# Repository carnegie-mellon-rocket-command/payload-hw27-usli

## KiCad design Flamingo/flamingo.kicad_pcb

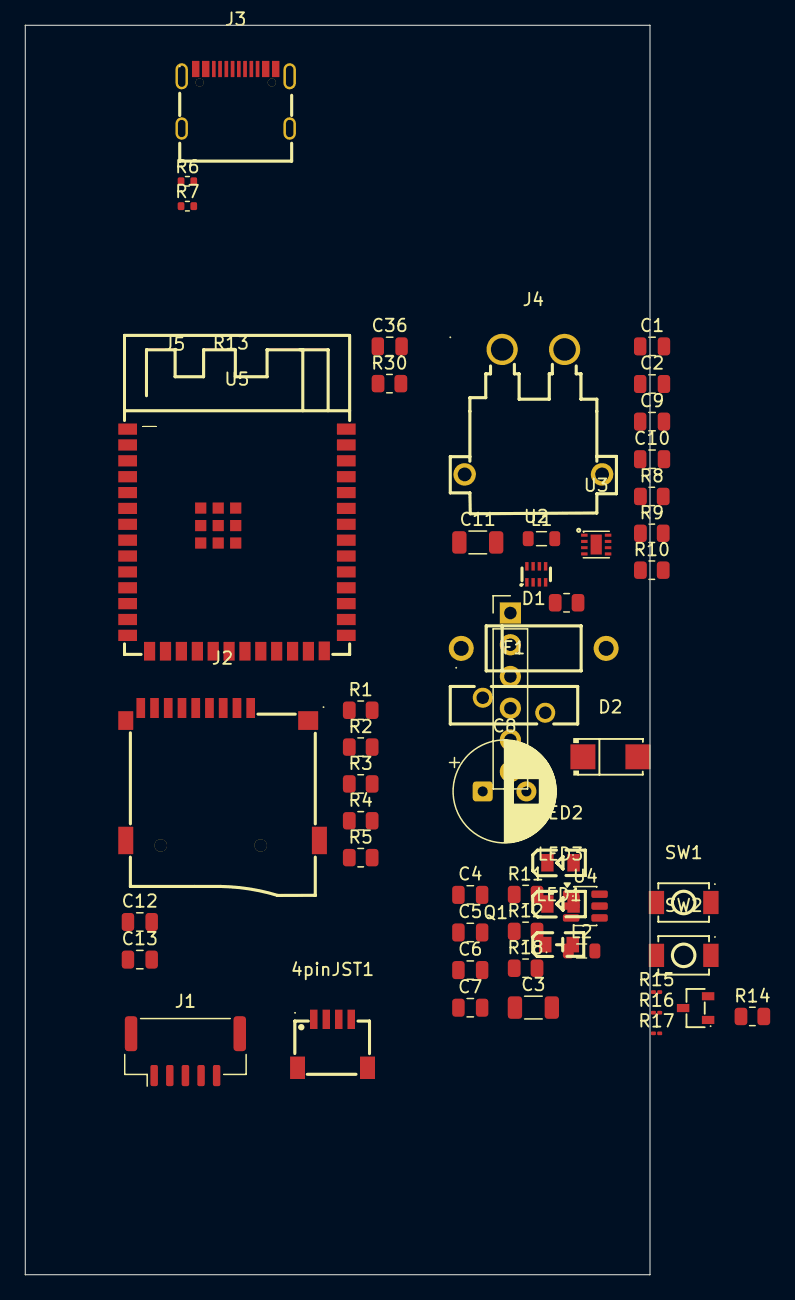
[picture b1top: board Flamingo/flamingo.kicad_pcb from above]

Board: 2 copper layers, 50.0 x 100.0 mm, 54 parts (0 on the bottom side), 43 nets, no tracks yet.

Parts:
4pinJST1: SM04B-SRSS-TB; CONN-SMD_4P-P1.00_SM04B-SRSS-TB-LF-SN
C1, C13: 10uF; C_0805_2012Metric
C2, C4, C5: 22uF; C_0805_2012Metric
C3: 10uF; C_1206_3216Metric
C6, C7, C12: 0.1uF; C_0805_2012Metric
C8: 47uF; CP_Radial_D8.0mm_P3.50mm
C9, C10: 4.7uF; C_0805_2012Metric
C11: 100uF; C_1206_3216Metric
C36: 1uF; C_0805_2012Metric
D1: P6KE20A; DO-15_BD3.1-L6.7-P10.70-D0.9-RD
D2: SS34; SMA_L4.3-W2.6-LS5.2-RD
F1: MF-R160; FUSE-TH_L10.2-W3.0-P5.10-D0.8-S1.20
J1: STA-M020X; JST_GH_BM05B-GHS-TBT_1x05-1MP_P1.25mm_Vertical
J2: TF-115-BCP9; TF-SMD_TF-115-BCP9
J3: USB-TYPE-C-017; USB-TYPE-C-SMD_C9900008089
J4: XT30PW-M30.G.Y; CONN-TH_XT30PW-M
J5: ARDUCAM_MEGA_SPI; PinHeader_1x06_P2.54mm_Vertical
L1: 2.2uH; L_0805_2012Metric
L2: 10uH; L_0805_2012Metric
LED1: XL-2012SURC; LED0805-RD
LED2, LED3: 0805G; LED0805-R-RD
Q1: AO3400A; SOT-23-3_L2.9-W1.3-P1.90-LS2.4-BR
R1, R2, R3, R4, R5, R8, R11, R13, R30: 10k; R_0805_2012Metric
R6, R7: 5.1k; R_0402_1005Metric
R9: 33k; R_0805_2012Metric
R10, R14, R18: 100k; R_0805_2012Metric
R12: 3.3k; R_0805_2012Metric
R15: 470; R_01005_0402Metric
R16, R17: 1k; R_01005_0402Metric
SW1, SW2: TS-1088-AR02016; SW-SMD_L3.9-W3.0-P4.45
U2: TPS2116DRLR; SOT-583-8_L2.1-W1.6-P0.50-LS1.6-BL
U3: TPS62162DSGR; WSON-8_L2.0-W2.0-P0.50-TL-EP
U4: TPS54302DDCR; SOT-23-6
U5: ESP32-S3-WROOM-1; WIRELM-SMD_ESP32-S3-WROOM-1

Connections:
3V3: J5.1, R13.2, R17.2
+3V3: C2.1, C12.1, C13.1, J2.4 (VDD), L1.2, R1.1, R2.1, R3.1, R4.1, R5.1, R10.2, R30.1, U3.6 (VOS), U5.2 (3V3)
/Arducam Mega SPI camera/CAM_CS: J5.6, R13.1, U5.7 (IO7)
/Arducam Mega SPI camera/CAM_MISO: J5.4, U5.17 (IO9)
/Arducam Mega SPI camera/CAM_MOSI: J5.5, U5.18 (IO10)
/Arducam Mega SPI camera/CAM_SCK: J5.3, U5.12 (IO8)
/Debug/DIAG_FAULT: R15.2, U5.11 (IO18)
/Debug/DIAG_HEARTBEAT: R16.2, U5.23 (IO21)
/Debug/DIAG_LED_EN: Q1.1 (G), R14.1, U5.10 (IO17)
/Debug/ESP_BOOT: SW2.1, U5.27 (IO0)
/Debug/LED_RETURN: LED1.1 (-), LED2.2 (K), Q1.3 (D)
/ESP32-S3 core/FC_UART_RX: 4pinJST1.3, U5.38 (IO2)
/ESP32-S3 core/FC_UART_TX: 4pinJST1.4, U5.39 (IO1)
/ESP32-S3 core/LASER_RX: J1.4, U5.32 (IO39)
/ESP32-S3 core/LASER_TX: J1.3, U5.31 (IO38)
/ESP32-S3 core/SD_CLK: J2.5 (CLK), U5.33 (IO40)
/ESP32-S3 core/USB_D_N: J3.A7 (DN1), J3.B7 (DN2), U5.13 (IO19)
/ESP32-S3 core/USB_D_P: J3.A6 (DP1), J3.B6 (DP2), U5.14 (IO20)
/Power/4S to 5 V buck/VBAT_PROT: C3.1, C6.1, C8.1, D1.1 (C), D2.1 (K), U4.3 (VIN)
/Power/BUCK_5V: C4.1, C5.1, C9.2, L2.2, R18.1, U2.6 (VIN2)
/Power/Input Protection/VBAT_4S: F1.1, J4.2 (+)
/Power/PR1: R8.2, R9.1, U2.4 (PR1)
/Power/USB_5V: C10.2, J3.A4B9 (VBUS), J3.B4A9 (VBUS), R9.2, U2.3 (VIN1), U2.5 (MODE)
/microSD/SD_CS: J2.2 (CD/DATA3), R2.2, U5.24 (IO47)
/microSD/SD_DAT1: J2.8 (DAT1), R5.2
/microSD/SD_DAT2: J2.1 (DATA2), R1.2
/microSD/SD_MISO: J2.7 (DAT0), R4.2, U5.35 (IO42)
/microSD/SD_MOSI: J2.3 (CMD), R3.2, U5.34 (IO41)
ESP_EN: C36.1, R30.2, SW1.1, U5.3 (EN)
GND: 4pinJST1.1, 4pinJST1.5, 4pinJST1.6, C1.2, C2.2, C3.2, C4.2, C5.2, C6.2, C8.2, C9.1, C10.1, C11.1, C12.2, C13.2, C36.2, D1.2 (A), J1.1, J2.6 (VSS), J2.10 (GND), J2.11 (GND), J2.12 (GND), J2.13 (GND), J3.1, J3.2, J3.3, J3.4, J3.A1B12 (GND), J3.B1A12 (GND), J4.1 (-), J4.3, J4.4, J5.2, LED3.2 (K), Q1.2 (S), R6.2, R7.2, R8.1, R12.1, R14.2, SW1.2, SW2.2, U2.1 (GND), U3.1 (PGND), U3.4 (AGND), U3.5 (FB), U3.9 (EP), U4.1 (GND), U5.1 (GND), U5.40 (GND), U5.41 (GND)
unnamed: D2.2 (A), F1.2
unnamed: J3.A5 (CC1), R7.1
unnamed: J3.B5 (CC2), R6.1
unnamed: LED1.2 (+), R15.1
unnamed: LED2.1 (A), R16.1
unnamed: LED3.1 (A), R17.1
unnamed: R11.1, R12.2
unnamed: R10.1, U3.8 (PG)
unnamed: L1.1, U3.7 (SW)
unnamed: C7.1, U4.6 (BOOT)
unnamed: R11.2, R18.2, U4.4 (FB)
unnamed: C7.2, L2.1, U4.2 (SW)
SYS_5V: C1.1, C11.2, J1.2, U2.2 (VOUT), U2.7 (VOUT), U3.2 (VIN), U3.3 (EN)

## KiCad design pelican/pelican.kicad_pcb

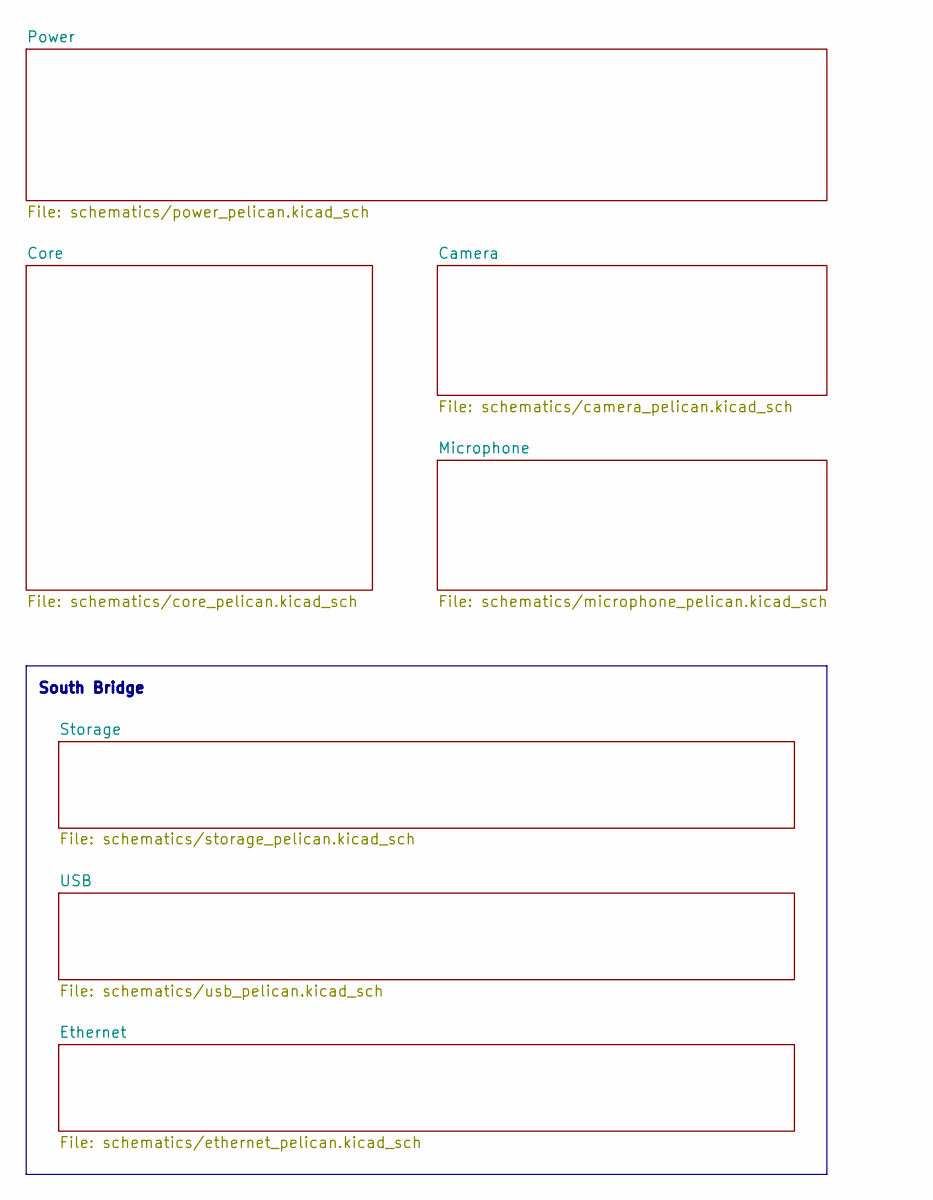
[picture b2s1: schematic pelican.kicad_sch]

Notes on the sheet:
South Bridge

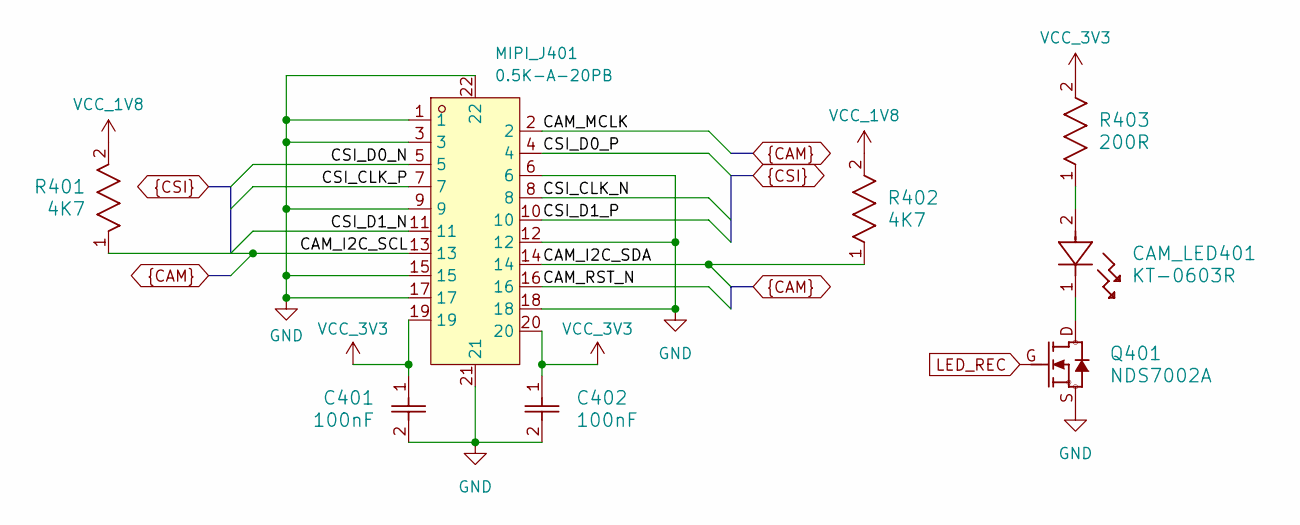
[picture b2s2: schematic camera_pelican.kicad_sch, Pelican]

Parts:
C401, C402: 100nF; C_GRM155R71C104KA88D; LCSC Part # C1525
CAM_LED401: KT-0603R; LED_LTST-C193KRKT-5A; LCSC Part # C2286
MIPI_J401: 0.5K-A-20PB; J_0.5K-A-20PB; MPN 0.5K-A-20PB; LCSC Part C2914144
Q401: NDS7002A; Q_NDS7002A; LCSC Part # C74715
R401, R402: 4K7; R_RC0402FR; LCSC Part # C25900
R403: 200R; R_RC0402FR; LCSC Part # C25087

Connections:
CAM_I2C_SCL: MIPI_J401.13, R401.1; also elsewhere on the board
CAM_I2C_SDA: MIPI_J401.14, R402.1; also elsewhere on the board
CAM_MCLK: MIPI_J401.2; also elsewhere on the board
CAM_RST_N: MIPI_J401.16; also elsewhere on the board
CSI_CLK_N: MIPI_J401.8; also elsewhere on the board
CSI_CLK_P: MIPI_J401.7; also elsewhere on the board
CSI_D0_N: MIPI_J401.5; also elsewhere on the board
CSI_D0_P: MIPI_J401.4; also elsewhere on the board
CSI_D1_N: MIPI_J401.11; also elsewhere on the board
CSI_D1_P: MIPI_J401.10; also elsewhere on the board
GND: C401.2, C402.2, MIPI_J401.1, MIPI_J401.3, MIPI_J401.6, MIPI_J401.9, MIPI_J401.12, MIPI_J401.15, MIPI_J401.17, MIPI_J401.18, MIPI_J401.21, MIPI_J401.22, Q401.S; also elsewhere on the board
LED_REC: Q401.G; also elsewhere on the board
unnamed: CAM_LED401.1, Q401.D
unnamed: CAM_LED401.2, R403.1
VCC_1V8: R401.2, R402.2; also elsewhere on the board
VCC_3V3: C401.1, C402.1, MIPI_J401.19, MIPI_J401.20, R403.2; also elsewhere on the board

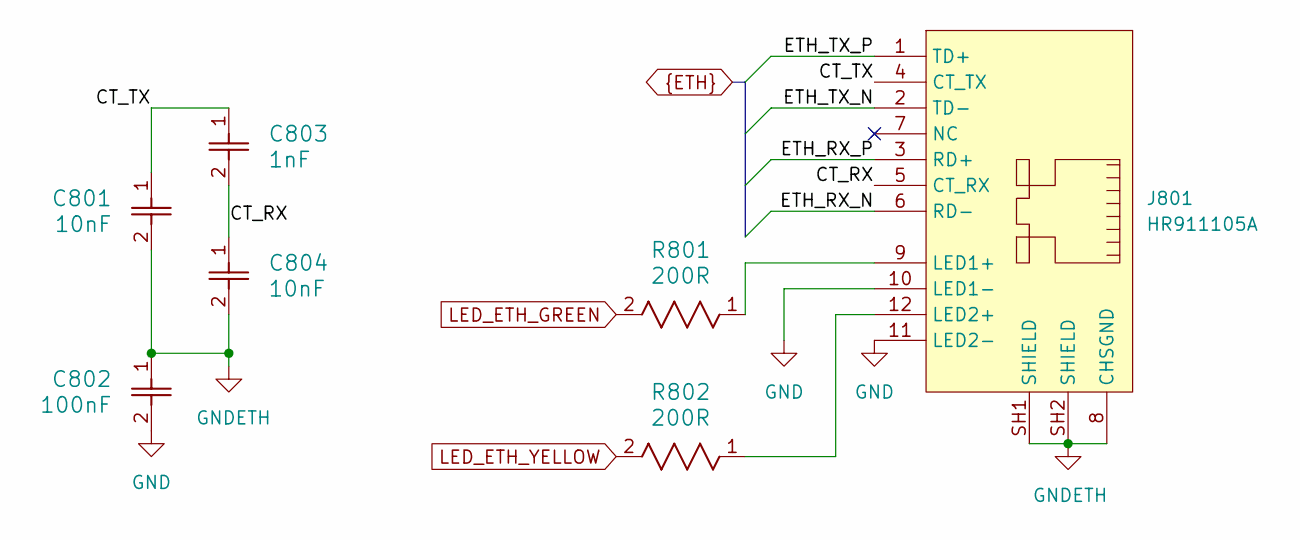
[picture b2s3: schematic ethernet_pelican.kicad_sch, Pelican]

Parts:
C801, C804: 10nF; C_CL05B103KO5NNNC; MPN CL05B103KO5NNNC; LCSC Part # C15195
C802: 100nF; C_GRM155R71C104KA88D; LCSC Part # C1525
C803: 1nF; C_CC0603CG100V102JN; MPN CC0603CG100V102JN; LCSC Part # C53084479
J801: HR911105A; J_HR911105A_TH; MPN HR911105A; LCSC Part C12074
R801, R802: 200R; R_RC0402FR; LCSC Part # C25087

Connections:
/Ethernet/CT_RX: C803.2, C804.1, J801.5 (CT_RX)
/Ethernet/CT_TX: C801.1, C803.1, J801.4 (CT_TX)
ETH_RX_N: J801.6 (RD-); also elsewhere on the board
ETH_RX_P: J801.3 (RD+); also elsewhere on the board
ETH_TX_N: J801.2 (TD-); also elsewhere on the board
ETH_TX_P: J801.1 (TD+); also elsewhere on the board
GND: C802.2, J801.10 (LED1-), J801.11 (LED2-); also elsewhere on the board
GNDETH: C801.2, C802.1, C804.2, J801.8 (CHSGND), J801.SH1 (SHIELD), J801.SH2 (SHIELD)
LED_ETH_GREEN: R801.2; also elsewhere on the board
LED_ETH_YELLOW: R802.2; also elsewhere on the board
unnamed: J801.9 (LED1+), R801.1
unnamed: J801.12 (LED2+), R802.1

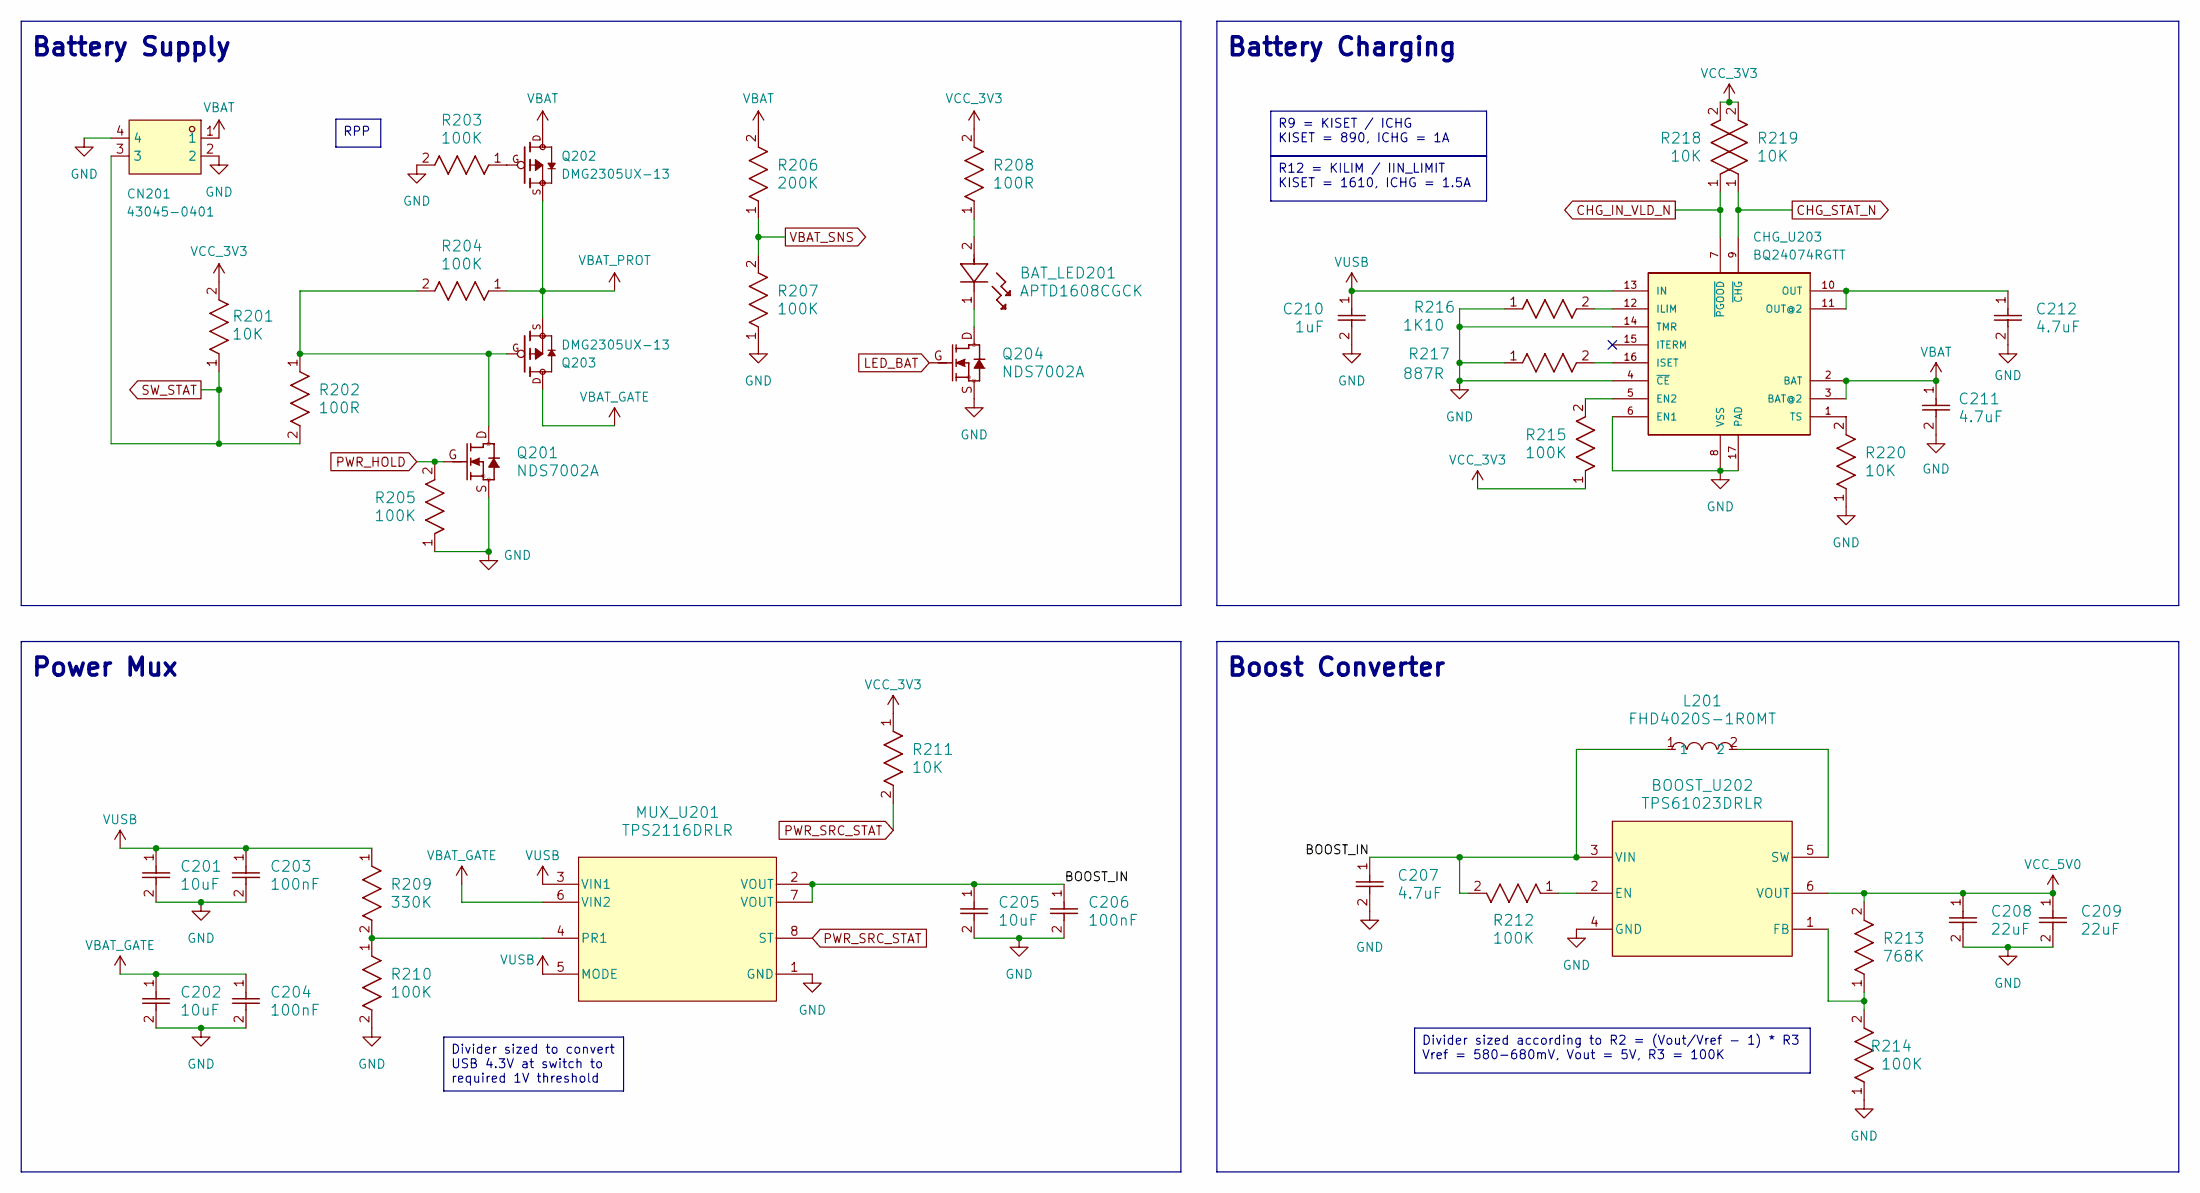
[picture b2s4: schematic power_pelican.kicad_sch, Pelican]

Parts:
BAT_LED201: APTD1608CGCK; LED_LTST-C193KGKT-5A; LCSC Part # C5121471
BOOST_U202: TPS61023DRLR; U_TPS61023DRLR; LCSC Part # C919459
C201, C202, C205: 10uF; C_GRM155R61A106ME11D; LCSC Part # C408132
C203, C204, C206: 100nF; C_GRM155R71C104KA88D; LCSC Part # C1525
C207, C211, C212: 4.7uF; C_GRM188R61A475KE15D; LCSC Part # C19666
C208, C209: 22uF; C_GRM188R61A226ME15D; LCSC Part # C84419
C210: 1uF; C_GRM155R61A105KE15D; LCSC Part # C52923
CHG_U203: BQ24074RGTT; U_BQ24074RGTT; LCSC Part # C2861252
CN201: 43045-0401; J_43045-0401_2x02_RA; MPN 430450401; LCSC Part C585880
L201: FHD4020S-1R0MT; L_FHD4020S-1R0MT; MPN FHD4020S-1R0MT; LCSC Part # C602028
MUX_U201: TPS2116DRLR; U_TPS2116DRLR; LCSC Part # C3235557
Q201, Q204: NDS7002A; Q_NDS7002A; LCSC Part # C74715
Q202, Q203: DMG2305UX-13; Q_DMG2305UX-13; PARTREV 09/2018; LCSC Part # C144153
R201, R211, R218, R219, R220: 10K; R_RC0402FR; LCSC Part # C25744
R202, R208: 100R; R_RC0402FR; LCSC Part # C25076
R203, R204, R205, R207, R210, R212, R214, R215: 100K; R_RC0402FR; LCSC Part # C25741
R206: 200K; R_RC0402FR; LCSC Part # C25764
R209: 330K; R_RC0402FR; LCSC Part # C25778
R213: 768K; R_RC0402FR; LCSC Part # C273722
R216: 1K10; R_RC0402FR; LCSC Part # C25860
R217: 887R; R_RC0402FR; LCSC Part # C477810

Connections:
/Power/BOOST_IN: BOOST_U202.3 (VIN), C205.1, C206.1, C207.1, L201.1, MUX_U201.2 (VOUT), MUX_U201.7 (VOUT), R212.2
CHG_IN_VLD_N: CHG_U203.7 (~PGOOD), R218.1; also elsewhere on the board
CHG_STAT_N: CHG_U203.9 (~CHG), R219.1; also elsewhere on the board
GND: BOOST_U202.4 (GND), C201.2, C202.2, C203.2, C204.2, C205.2, C206.2, C207.2, C208.2, C209.2, C210.2, C211.2, C212.2, CHG_U203.4 (~CE), CHG_U203.6 (EN1), CHG_U203.8 (VSS), CHG_U203.14 (TMR), CHG_U203.17 (PAD), CN201.2, CN201.4, MUX_U201.1 (GND), Q201.S, Q204.S, R203.2, R205.1, R207.1, R210.2, R214.1, R216.1, R217.1, R220.1; also elsewhere on the board
LED_BAT: Q204.G; also elsewhere on the board
unnamed: BAT_LED201.1, Q204.D
unnamed: BAT_LED201.2, R208.1
unnamed: BOOST_U202.2 (EN), R212.1
unnamed: BOOST_U202.1 (FB), R213.1, R214.2
unnamed: BOOST_U202.5 (SW), L201.2
unnamed: CHG_U203.5 (EN2), R215.2
unnamed: CHG_U203.12 (ILIM), R216.2
unnamed: CHG_U203.16 (ISET), R217.2
unnamed: C212.1, CHG_U203.10 (OUT), CHG_U203.11 (OUT@2)
unnamed: CHG_U203.1 (TS), R220.2
unnamed: MUX_U201.4 (PR1), R209.2, R210.1
unnamed: Q201.D, Q203.G, R202.1, R204.2
unnamed: Q202.G, R203.1
unnamed: Q202.S, Q203.S, R204.1
PWR_HOLD: Q201.G, R205.2; also elsewhere on the board
PWR_SRC_STAT: MUX_U201.8 (ST), R211.2; also elsewhere on the board
SW_STAT: CN201.3, R201.1, R202.2; also elsewhere on the board
VBAT: C211.1, CHG_U203.2 (BAT), CHG_U203.3 (BAT@2), CN201.1, Q202.D, R206.2
VBAT_SNS: R206.1, R207.2; also elsewhere on the board
VCC_3V3: R201.2, R208.2, R211.1, R215.1, R218.2, R219.2; also elsewhere on the board
VCC_5V0: BOOST_U202.6 (VOUT), C208.1, C209.1, R213.2; also elsewhere on the board
VUSB: C201.1, C203.1, C210.1, CHG_U203.13 (IN), MUX_U201.3 (VIN1), MUX_U201.5 (MODE), R209.1; also elsewhere on the board

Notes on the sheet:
Battery Charging
Power Mux
Battery Supply
Boost Converter
Divider sized according to R2 = (Vout/Vref - 1) * R3 Vref = 580-680mV, Vout = 5V, R3 = 100K
R12 = KILIM / IIN_LIMIT KISET = 1610, ICHG = 1.5A
R9 = KISET / ICHG KISET = 890, ICHG = 1A
Divider sized to convert USB 4.3V at switch to required 1V threshold
RPP

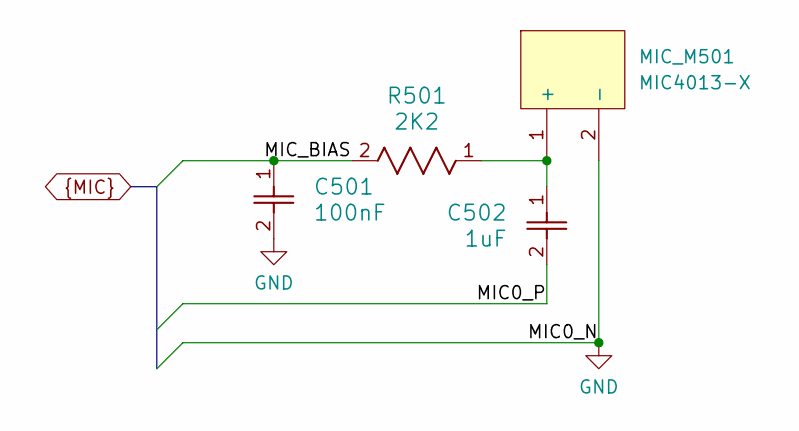
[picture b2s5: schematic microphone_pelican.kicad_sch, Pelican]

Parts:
C501: 100nF; C_GRM155R71C104KA88D; LCSC Part # C1525
C502: 1uF; C_GRM155R61A105KE15D; LCSC Part # C52923
MIC_M501: MIC4013-X; M_MIC4013-X; MPN MIC4013-X; LCSC Part # C49118137
R501: 2K2; R_RC0402FR; LCSC Part # C25879

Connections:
GND: C501.2, MIC_M501.2 (-); also elsewhere on the board
MIC0_P: C502.2; also elsewhere on the board
MIC_BIAS: C501.1, R501.2; also elsewhere on the board
unnamed: C502.1, MIC_M501.1 (+), R501.1

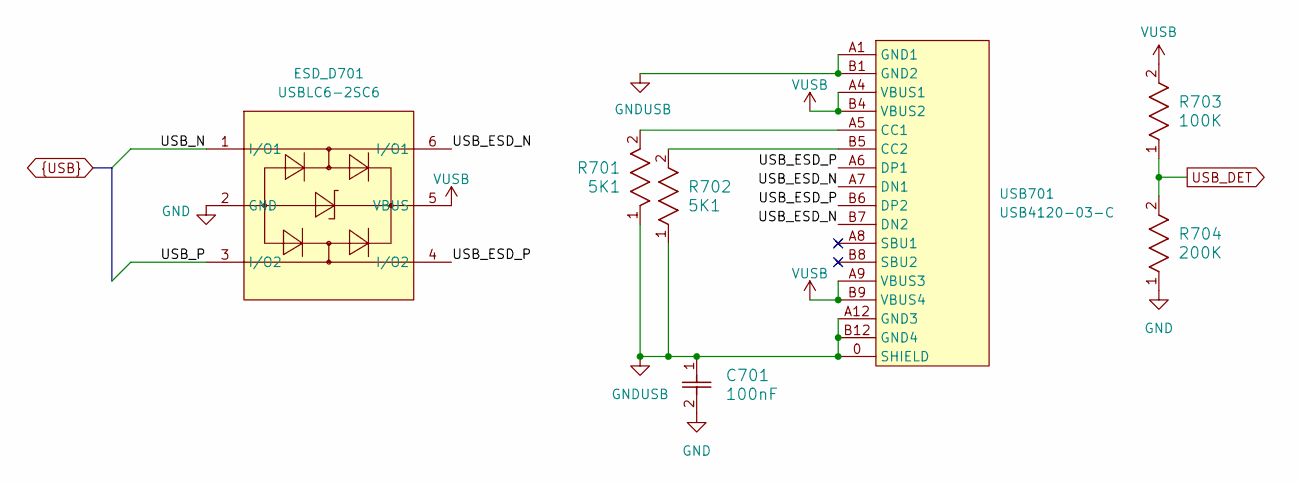
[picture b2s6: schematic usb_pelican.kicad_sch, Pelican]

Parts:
C701: 100nF; C_GRM155R71C104KA88D; LCSC Part # C1525
ESD_D701: USBLC6-2SC6; D_USBLC6-2SC6; MPN USBLC6-2SC6; LCSC Part # C7519
R701, R702: 5K1; R_RC0402FR; LCSC Part # C25905
R703: 100K; R_RC0402FR; LCSC Part # C25741
R704: 200K; R_RC0402FR; LCSC Part # C25764
USB701: USB4120-03-C; J_USB4120-03-C_SMD; MPN USB4120-03-C; LCSC Part C3445864

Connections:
/USB/USB_ESD_N: ESD_D701.6 (I/O1), USB701.A7 (DN1), USB701.B7 (DN2)
/USB/USB_ESD_P: ESD_D701.4 (I/O2), USB701.A6 (DP1), USB701.B6 (DP2)
GND: C701.2, ESD_D701.2 (GND), R704.1; also elsewhere on the board
GNDUSB: C701.1, R701.1, R702.1, USB701.0 (SHIELD), USB701.A1 (GND1), USB701.A12 (GND3), USB701.B1 (GND2), USB701.B12 (GND4)
unnamed: R701.2, USB701.A5 (CC1)
unnamed: R702.2, USB701.B5 (CC2)
USB_DET: R703.1, R704.2; also elsewhere on the board
USB_N: ESD_D701.1 (I/O1); also elsewhere on the board
USB_P: ESD_D701.3 (I/O2); also elsewhere on the board
VUSB: ESD_D701.5 (VBUS), R703.2, USB701.A4 (VBUS1), USB701.A9 (VBUS3), USB701.B4 (VBUS2), USB701.B9 (VBUS4); also elsewhere on the board

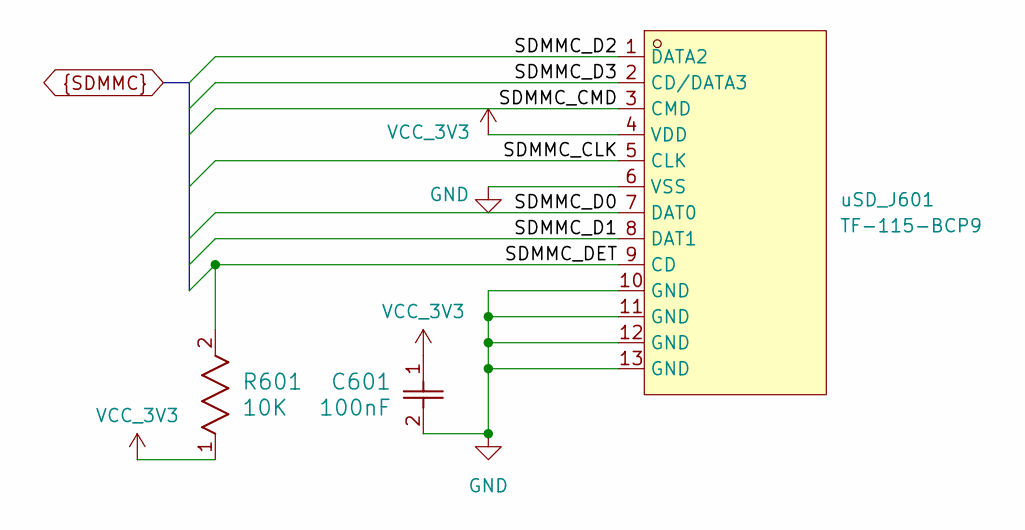
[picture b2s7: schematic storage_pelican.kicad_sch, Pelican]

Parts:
C601: 100nF; C_GRM155R71C104KA88D; LCSC Part # C1525
R601: 10K; R_RC0402FR; LCSC Part # C25744
uSD_J601: TF-115-BCP9; J_TF-115-BCP9; MPN TF-115-BCP9; LCSC Part # C720505

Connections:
GND: C601.2, uSD_J601.6 (VSS), uSD_J601.10 (GND), uSD_J601.11 (GND), uSD_J601.12 (GND), uSD_J601.13 (GND); also elsewhere on the board
SDMMC_CLK: uSD_J601.5 (CLK); also elsewhere on the board
SDMMC_CMD: uSD_J601.3 (CMD); also elsewhere on the board
SDMMC_D0: uSD_J601.7 (DAT0); also elsewhere on the board
SDMMC_D1: uSD_J601.8 (DAT1); also elsewhere on the board
SDMMC_D2: uSD_J601.1 (DATA2); also elsewhere on the board
SDMMC_D3: uSD_J601.2 (CD/DATA3); also elsewhere on the board
SDMMC_DET: R601.2, uSD_J601.9 (CD); also elsewhere on the board
VCC_3V3: C601.1, R601.1, uSD_J601.4 (VDD); also elsewhere on the board

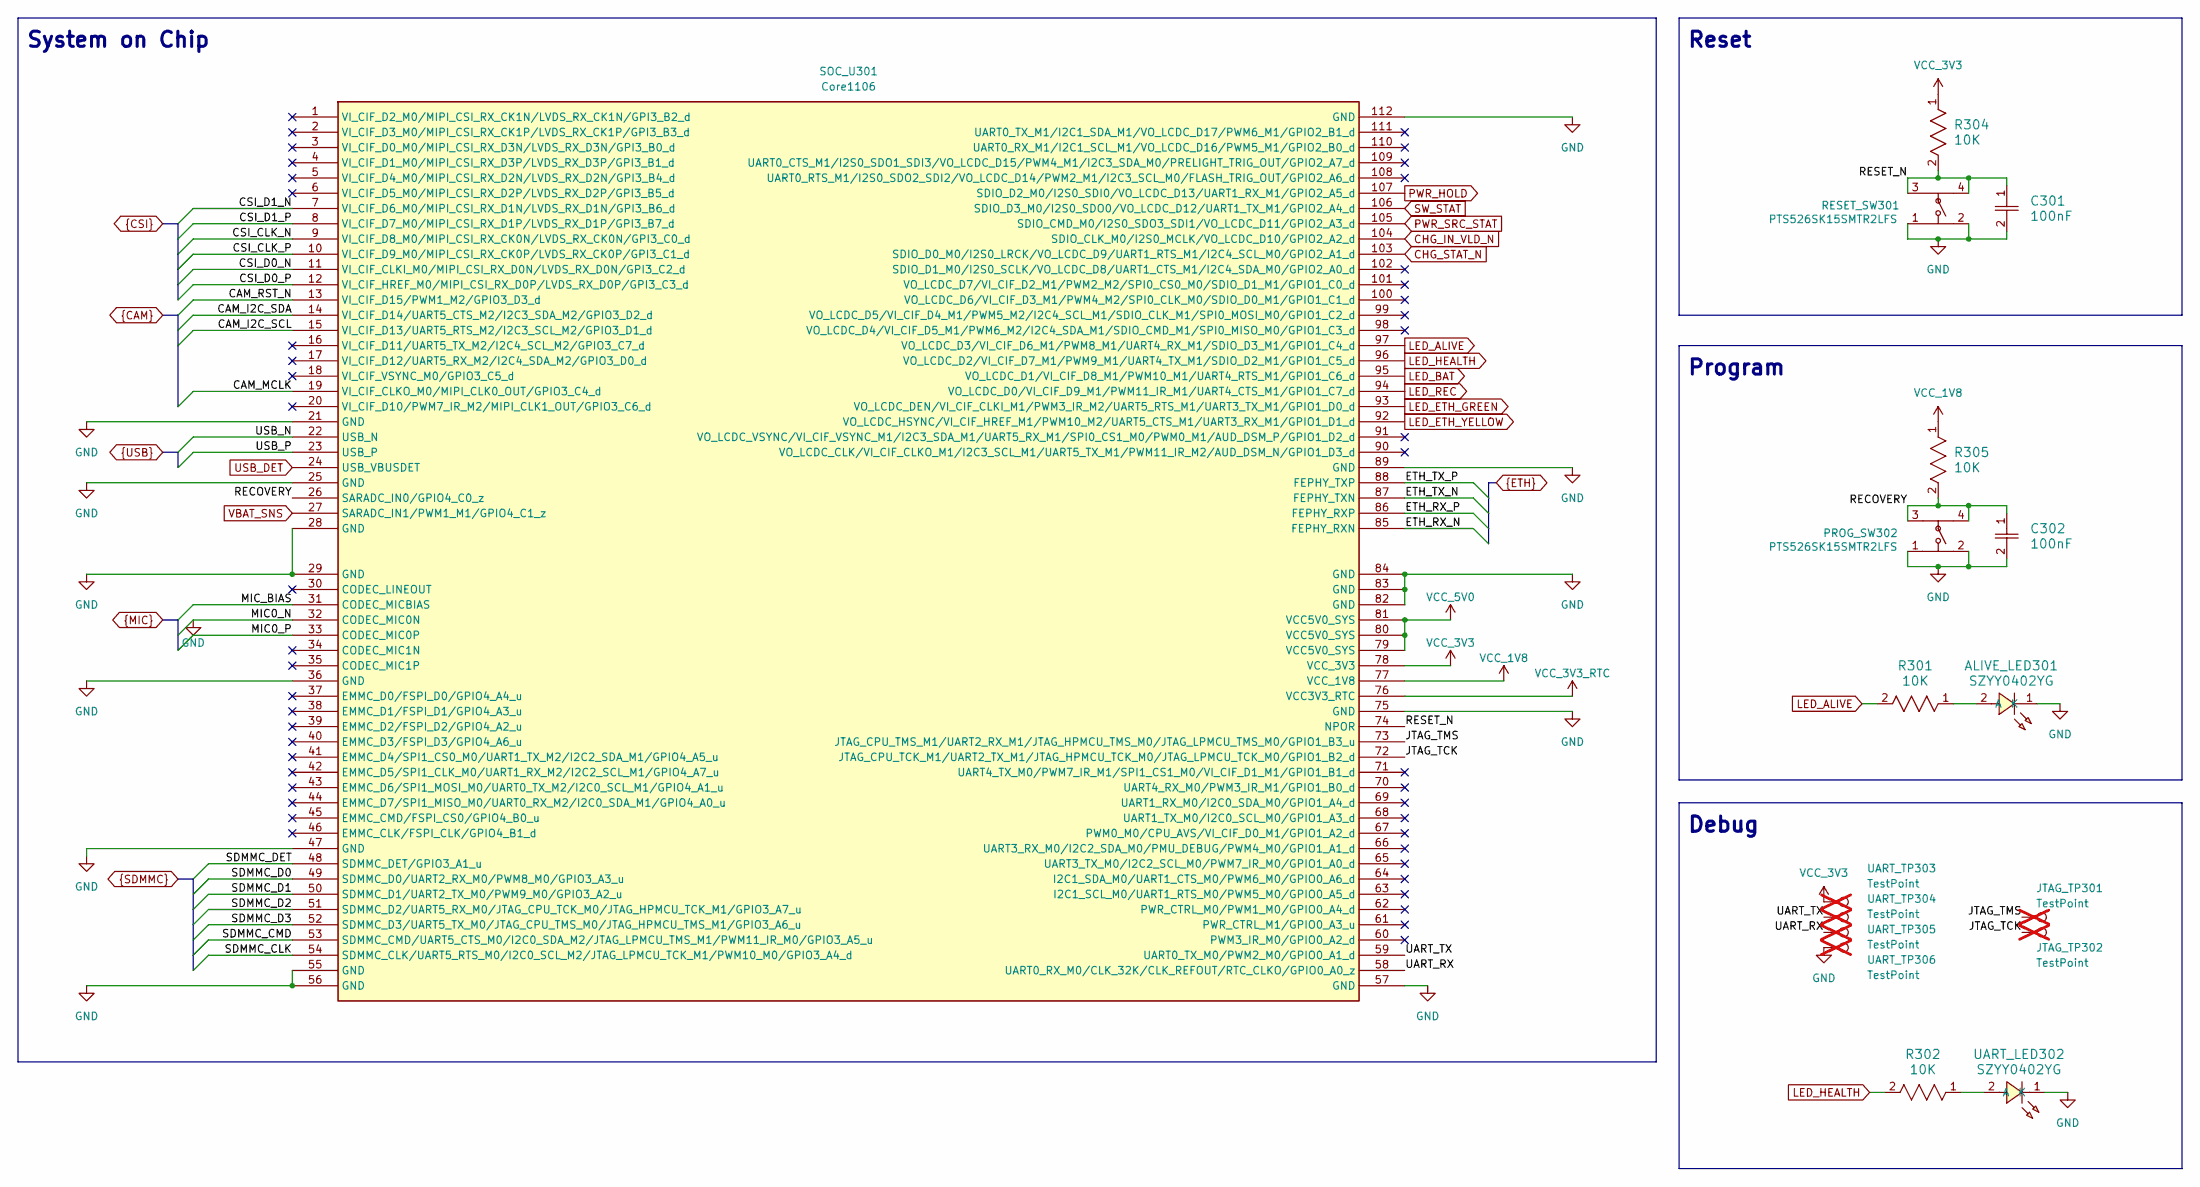
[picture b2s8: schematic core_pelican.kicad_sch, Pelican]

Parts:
ALIVE_LED301: SZYY0402YG; LED_SZYY0402YG; MPN SZYY0402YG; LCSC Part # C434449
C301, C302: 100nF; C_GRM155R71C104KA88D; LCSC Part # C1525
JTAG_TP301, JTAG_TP302: TestPoint; TestPoint_Pad_D1.5mm; not fitted
PROG_SW302: PTS526SK15SMTR2LFS; SW_PTS526SK15SMTR2LFS; LCSC Part # C2689521
R301, R302, R304, R305: 10K; R_RC0402FR; LCSC Part # C25744
RESET_SW301: PTS526SK15SMTR2LFS; SW_PTS526SK15SMTR2LFS; LCSC Part # C2689521
SOC_U301: Core1106; P_Core1106
UART_LED302: SZYY0402YG; LED_SZYY0402YG; MPN SZYY0402YG; LCSC Part # C434449
UART_TP303, UART_TP304, UART_TP305, UART_TP306: TestPoint; TestPoint_Pad_D1.5mm; not fitted

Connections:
/Core/JTAG_TCK: JTAG_TP302.1 (1_1), SOC_U301.72 (JTAG_CPU_TCK_M1/UART2_TX_M1/JTAG_HPMCU_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)
/Core/JTAG_TMS: JTAG_TP301.1 (1_1), SOC_U301.73 (JTAG_CPU_TMS_M1/UART2_RX_M1/JTAG_HPMCU_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)
/Core/RECOVERY: C302.1, PROG_SW302.3, PROG_SW302.4, R305.2, SOC_U301.26 (SARADC_IN0/GPIO4_C0_z)
/Core/RESET_N: C301.1, R304.2, RESET_SW301.3, RESET_SW301.4, SOC_U301.74 (NPOR)
/Core/UART_RX: SOC_U301.58 (UART0_RX_M0/CLK_32K/CLK_REFOUT/RTC_CLKO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), UART_TP305.1 (1_1)
/Core/UART_TX: SOC_U301.59 (UART0_TX_M0/PWM2_M0/GPIO0_A1_d), UART_TP304.1 (1_1)
CAM_I2C_SCL: SOC_U301.15 (VI_CIF_D13/UART5_RTS_M2/I2C3_SCL_M2/GPI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); also elsewhere on the board
CAM_I2C_SDA: SOC_U301.14 (VI_CIF_D14/UART5_CTS_M2/I2C3_SDA_M2/GPI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); also elsewhere on the board
CAM_MCLK: SOC_U301.19 (VI_CIF_CLKO_M0/MIPI_CLK0_OUT/GPIO3_C4_d); also elsewhere on the board
CAM_RST_N: SOC_U301.13 (VI_CIF_D15/PWM1_M2/GPIO3_D3_d); also elsewhere on the board
CHG_IN_VLD_N: SOC_U301.104 (SDIO_CLK_M0/I2S0_MCLK/VO_LCDC_D10/GPIO2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); also elsewhere on the board
CHG_STAT_N: SOC_U301.103 (SDIO_D0_M0/I2S0_LRCK/VO_LCDC_D9/UART1_R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); also elsewhere on the board
CSI_CLK_N: SOC_U301.9 (VI_CIF_D8_M0/MIPI_CSI_RX_CK0N/LVDS_RX_C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); also elsewhere on the board
CSI_CLK_P: SOC_U301.10 (VI_CIF_D9_M0/MIPI_CSI_RX_CK0P/LVDS_RX_C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); also elsewhere on the board
CSI_D0_N: SOC_U301.11 (VI_CIF_CLKI_M0/MIPI_CSI_RX_D0N/LVDS_RX_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); also elsewhere on the board
CSI_D0_P: SOC_U301.12 (VI_CIF_HREF_M0/MIPI_CSI_RX_D0P/LVDS_RX_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); also elsewhere on the board
CSI_D1_N: SOC_U301.7 (VI_CIF_D6_M0/MIPI_CSI_RX_D1N/LVDS_RX_D1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); also elsewhere on the board
CSI_D1_P: SOC_U301.8 (VI_CIF_D7_M0/MIPI_CSI_RX_D1P/LVDS_RX_D1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); also elsewhere on the board
ETH_RX_N: SOC_U301.85 (FEPHY_RXN); also elsewhere on the board
ETH_RX_P: SOC_U301.86 (FEPHY_RXP); also elsewhere on the board
ETH_TX_N: SOC_U301.87 (FEPHY_TXN); also elsewhere on the board
ETH_TX_P: SOC_U301.88 (FEPHY_TXP); also elsewhere on the board
GND: ALIVE_LED301.1 (K), C301.2, C302.2, PROG_SW302.1, PROG_SW302.2, RESET_SW301.1, RESET_SW301.2, SOC_U301.21 (GND), SOC_U301.25 (GND), SOC_U301.28 (GND), SOC_U301.29 (GND), SOC_U301.32 (CODEC_MIC0N), SOC_U301.36 (GND), SOC_U301.47 (GND), SOC_U301.55 (GND), SOC_U301.56 (GND), SOC_U301.57 (GND), SOC_U301.75 (GND), SOC_U301.82 (GND), SOC_U301.83 (GND), SOC_U301.84 (GND), SOC_U301.89 (GND), SOC_U301.112 (GND), UART_LED302.1 (K), UART_TP306.1 (1_1); also elsewhere on the board
LED_ALIVE: R301.2, SOC_U301.97 (VO_LCDC_D3/VI_CIF_D6_M1/PWM8_M1/UART4_R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)
LED_BAT: SOC_U301.95 (VO_LCDC_D1/VI_CIF_D8_M1/PWM10_M1/UART4_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); also elsewhere on the board
LED_ETH_GREEN: SOC_U301.93 (VO_LCDC_DEN/VI_CIF_CLKI_M1/PWM3_IR_M2/U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); also elsewhere on the board
LED_ETH_YELLOW: SOC_U301.92 (VO_LCDC_HSYNC/VI_CIF_HREF_M1/PWM10_M2/U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); also elsewhere on the board
LED_HEALTH: R302.2, SOC_U301.96 (VO_LCDC_D2/VI_CIF_D7_M1/PWM9_M1/UART4_T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)
LED_REC: SOC_U301.94 (VO_LCDC_D0/VI_CIF_D9_M1/PWM11_IR_M1/UAR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); also elsewhere on the board
MIC0_P: SOC_U301.33 (CODEC_MIC0P); also elsewhere on the board
MIC_BIAS: SOC_U301.31 (CODEC_MICBIAS); also elsewhere on the board
unnamed: ALIVE_LED301.2 (A), R301.1
unnamed: R302.1, UART_LED302.2 (A)
PWR_HOLD: SOC_U301.107 (SDIO_D2_M0/I2S0_SDI0/VO_LCDC_D13/UART1_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); also elsewhere on the board
PWR_SRC_STAT: SOC_U301.105 (SDIO_CMD_M0/I2S0_SDO3_SDI1/VO_LCDC_D11/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); also elsewhere on the board
SDMMC_CLK: SOC_U301.54 (SDMMC_CLK/UART5_RTS_M0/I2C0_SCL_M2/JTAG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); also elsewhere on the board
SDMMC_CMD: SOC_U301.53 (SDMMC_CMD/UART5_CTS_M0/I2C0_SDA_M2/JTAG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); also elsewhere on the board
SDMMC_D0: SOC_U301.49 (SDMMC_D0/UART2_RX_M0/PWM8_M0/GPIO3_A3_u); also elsewhere on the board
SDMMC_D1: SOC_U301.50 (SDMMC_D1/UART2_TX_M0/PWM9_M0/GPIO3_A2_u); also elsewhere on the board
SDMMC_D2: SOC_U301.51 (SDMMC_D2/UART5_RX_M0/JTAG_CPU_TCK_M0/JT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); also elsewhere on the board
SDMMC_D3: SOC_U301.52 (SDMMC_D3/UART5_TX_M0/JTAG_CPU_TMS_M0/JT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); also elsewhere on the board
SDMMC_DET: SOC_U301.48 (SDMMC_DET/GPIO3_A1_u); also elsewhere on the board
SW_STAT: SOC_U301.106 (SDIO_D3_M0/I2S0_SDO0/VO_LCDC_D12/UART1_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); also elsewhere on the board
USB_DET: SOC_U301.24 (USB_VBUSDET); also elsewhere on the board
USB_N: SOC_U301.22 (USB_N); also elsewhere on the board
USB_P: SOC_U301.23 (USB_P); also elsewhere on the board
VBAT_SNS: SOC_U301.27 (SARADC_IN1/PWM1_M1/GPIO4_C1_z); also elsewhere on the board
VCC_1V8: R305.1, SOC_U301.77 (VCC_1V8); also elsewhere on the board
VCC_3V3: R304.1, SOC_U301.78 (VCC_3V3), UART_TP303.1 (1_1); also elsewhere on the board
VCC_3V3_RTC: SOC_U301.76 (VCC3V3_RTC)
VCC_5V0: SOC_U301.79 (VCC5V0_SYS), SOC_U301.80 (VCC5V0_SYS), SOC_U301.81 (VCC5V0_SYS); also elsewhere on the board

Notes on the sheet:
Debug
System on Chip
Program
Reset

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
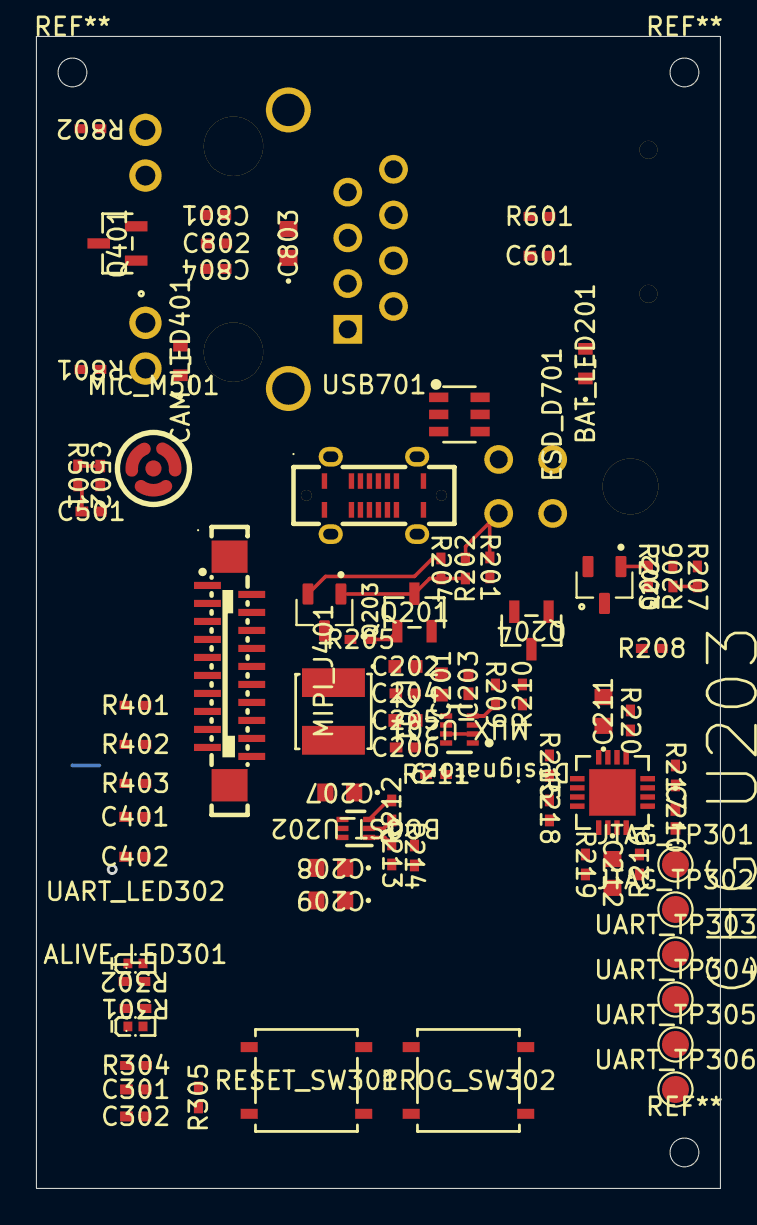
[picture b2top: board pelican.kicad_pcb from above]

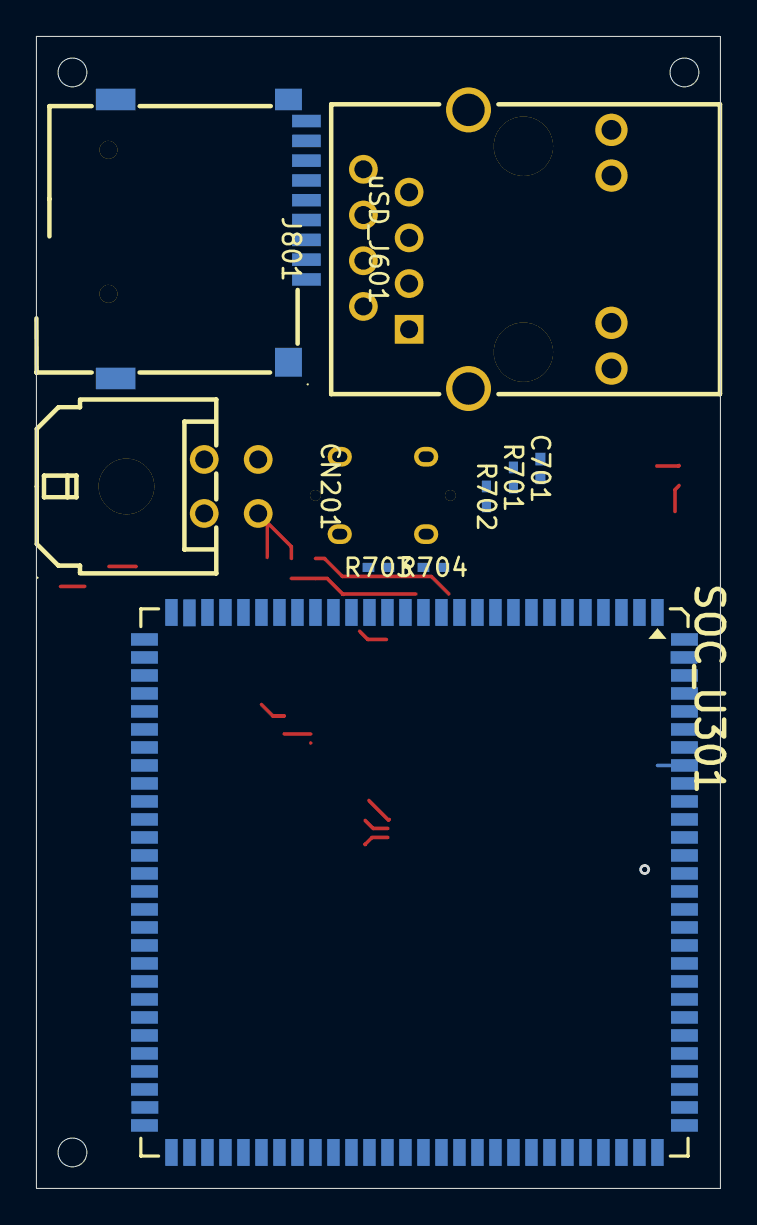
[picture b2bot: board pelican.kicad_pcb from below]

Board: 4 copper layers, 38.0 x 64.0 mm, 88 parts (9 on the bottom side), 82 nets.
